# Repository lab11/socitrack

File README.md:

TotTag
======

TotTag is a wearable device that measures **how close people are to one another**, continuously, with
no infrastructure in the room. Each device carries an ultra-wideband (UWB) radio and ranges against
every other device nearby twice a second, recording distances to on-board flash. Nothing is installed
in the environment, nothing is transmitted during a deployment, and no audio or video is captured.

If you are interested in using TotTag in your own research, please fill out this
[Interest Form](https://forms.gle/SqWca9DrKpcx9rBL6).

> **Note: This system is under heavy development and is provided as-is, with no mechanism for external
> support, technical or otherwise. In the future, once the project has reached a steady state and
> staffing has ramped up, we may begin providing limited support. We will post any updates on that
> front here. Thank you for your understanding!**

Documentation
-------------

**All user documentation lives at [lab11.github.io/socitrack](https://lab11.github.io/socitrack/),
built from [`docs/`](docs/).**

Start with [Running a Deployment](docs/running-a-deployment.md) if you want to use TotTag, or
[Getting Started](docs/getting-started.md) if you have devices that have never been set up.

Repository layout
-----------------

| Directory | Contents |
| --- | --- |
| [`docs/`](docs/) | All user and developer documentation; the source of the documentation site |
| [`software/`](software/) | Device firmware and the tools that configure devices and read their data |
| [`hardware/`](hardware/) | Board designs, bills of materials, and enclosure CAD |
| [`media/`](media/) | Photographs and diagrams used by the documentation |

TotTag saw a major platform refresh in 2023, moving to a new hardware and software design built
around the Ambiq Apollo4. Documentation describing the earlier generation is kept under
[`docs/archive/`](docs/archive/).

History, Related Projects, & Relevant Publications
==================================================

This current effort builds on a long line of work exploring the capabilities of
ultra wideband under resource-constrained settings. This repository is an
evolution of projects exploring COTS-based solutions; some others linked below
explore more custom ultra wideband as well.

SociTrack and TotTag Gen 1
--------------------------

- Salo, V. C., Pannuto, P., Hedgecock, W., Biri, A., Russo, D. A., Piersiak, H. A., & Humphreys, K. L. (2022). Measuring naturalistic proximity as a window into caregiver-child interaction patterns. Behavior research methods, 54(4), 1580–1594. https://doi.org/10.3758/s13428-021-01681-8

- Andreas Biri, Neal Jackson, Lothar Thiele, Pat Pannuto, and Prabal Dutta. 2020.
*SociTrack: Infrastructure-Free Interaction Tracking through Mobile Sensor Networks.*
In The 26th Annual International Conference on Mobile Computing and Networking
(MobiCom ’20), September 21–25, 2020, London, United Kingdom. ACM, New York, NY,
USA, 14 pages. https://doi.org/10.1145/3372224.3419190

<!--
- Andreas Biri, Pat Pannuto, and Prabal Dutta. 2019.
*Demo Abstract: Tot-Ternary - A Wearable Platform for Social Interaction Tracking.*
In The 18th International Conference on Information Processing in Sensor Networks
(co-located with CPS-IoT Week 2019) (IPSN ’19), April 16-18, 2019, Montreal, QC,
Canada. ACM, New York, NY, USA, 2 pages. https://doi.org/10.1145/3302506.3312486
-->

<details>
<summary>Legacy documentation from SociTrack / TotTag Gen 1
</summary>

SociTrack
=========

*SociTrack* is a system for using ultra-wideband RF time-of-flight processing to
perform indoor ranging and localization. It incorporates the *SquarePoint*
module, containing a DecaWave DW1000 radio for UWB packet transmission and
timestamping. This module provides node-to-node ranges over an I<sup>2</sup>C
interface which can then be stored locally or transmitted externally.

Hardware
--------

The **SociTrack** system is composed of several hardware pieces. At its core is
the *SquarePoint* module, a 30mm x 15mm PCB that encompasses all of the
core ranging hardware and firmware. *SquarePoint* is provided as an EAGLE board
that allows for direct integration as a design block as part of the
[Lab11 EAGLE library](https://github.com/lab11/eagle). One example of a project
that uses the *SquarePoint* module is the *TotTag*, which comprises an
all-in-one tracking and localization system for mobile nodes. The *TotTag*
hardware includes three UWB antennas and a Bluetooth Low Energy (BLE) radio,
plus a battery charging circuit, SD card for data logging, accelerometer, USB
connectivity, and integrated sensor fusion. TotTag is able to provide ranges and
position estimates directly to a mobile phone application in real-time and can
be configured on-the-fly using a simple user interface over
[Summon](https://github.com/lab11/summon).

### SquarePoint

SquarePoint, an EAGLE design block for UWB ranging, includes the following
components:

- DecaWave DW1000 UWB radio
- STMicroelectronics STM32F091CCU6 MCU
- RF switch

The MCU contains all of the necessary code to control the DW1000 and run the
ranging protocol. This module provides a simple abstraction layer for quick
integration with a carrier board over an I<sup>2</sup>C interface without having
to worry about any underlying implementation details.

### TotTag

The TotTag is a self-contained PCB which utilizes SquarePoint to provide ranging
data for human interaction tracking. It includes:

- The SquarePoint module - 3 UWB antennas
- Nordic Semiconductors nRF52840 BLE radio
- 3.3V LDO designed to be used with 4.2V LiPo batteries
- Battery charge management controller
- SD card holder
- microUSB connector including FTDI FT232R for debugging
- 3-axis accelerometer

The TotTag is designed to be a device that can be used as a ranging anchor, a
mobile tag, or a hybrid combination of both. It offers both infrastructure-free
and infrastructure-based network processing and allows for centimeter-accurate,
multi-day deployments. Both the schematic and board design are open-source and
can be found in the [`hardware/tottag`](hardware/tottag) folder; a suitable 3D
printable case is also provided in
[`hardware/cad/tottag-case`](hardware/cad/tottag-case/).

Software
--------

The SociTrack software is freely available as an open-source Git repository.
When cloning this repository, be sure to do

    git clone --recursive https://github.com/lab11/socitrack.git

or to later run

    git submodule init && git submodule sync

so that all submodules are cloned as well. All of the supporting libraries and
build tools are in submodules for the various hardware platforms used in this
project.

#### SquarePoint

Found in `software/squarepoint` (removed), the core firmware that
enables the SquarePoint module to work includes all of the logic implementing
our custom ranging protocol on top of the DecaWave DW1000 UWB radio. It makes
use of frequency and antenna diversity and leverages both one-way and two-way
ToF ranging to achieve efficient and reliable ranging in various environments.
The firmware architecture supports multiple runtime modalities that can
be selected on-the-fly; currently, we officially support:

- *Standard*: the full ranging protocol, using maximal diversity to achieve
              highly-reliable ranging measurements over 30 different channels.
- *Calibration*: automatically triggered by our calibration scripts, allowing
                 for automated board-specific calibration functions which are
                 then applied to future ranging measurements.

#### TotTag

The TotTag code, located in `software/tottag` (removed),
implements a BLE application that uses the SquarePoint module as an
I<sup>2</sup>C slave and provides for external BLE connectivity. It exposes BLE
services to configure and enable the device, to set the current time to enable
accurate timestamping of ranging data, as well as to access ranging data in
real-time.

#### Mobile App and BLE

The tools in the `software/tottag/mobile_app` (removed)
directory interact with TotTag and read data across the BLE interface. They uses
the Summon app ([Google Play](https://play.google.com/store/apps/details?id=edu.umich.eecs.lab11.summon),
[App Store](https://itunes.apple.com/us/app/summon-lab11/id1051205682)) to
easily access and interact with the TotTag devices. The target website must be
configured in the TotTag code and can be hosted on a personal domain; we
recommend the use of a link shortener to reduce the BLE advertisement length.

### Linux Development

This project requires the [GNU ARM Embedded Toolchain](https://developer.arm.com/open-source/gnu-toolchain/gnu-rm).
Please be aware that the some Linux distros provide out-of-date versions of this
tool; as such, we strongly recommend that you install the newest version
directly from ARM.

</details>

SurePoint
---------

The original projects exploring COTS UWB technology.

PolyPoint introduced the concept of antenna diversity, and demonstrated its
efficacy by finishing as the best-performing UWB-based system at the 2015
Microsoft Indoor Localization competition.

SurePoint expanded on the PolyPoint concepts and built a complete system around
efficient channel diversity, and showed how to scale up robust ranging with
COTS UWB.

- Benjamin Kempke, Pat Pannuto, Bradford Campbell, and Prabal Dutta. 2016.
*SurePoint: Exploiting ultra wideband flooding and diversity to provide robust, scalable, high-fidelity indoor localization.*
In Proceedings of the 14th ACM Conference on Embedded Network Sensor Systems
(SenSys ’16), November 14-16, 2016, Stanford, CA, USA.  ACM, New York, NY,
USA, 13 pages. https://doi.org/10.1145/2994551.2994570

- Benjamin Kempke, Pat Pannuto, and Prabal Dutta. 2015.
*PolyPoint: Guiding indoor quadrotors with ultra-wideband localization.*
In Proceedings of the 2nd International Workshop on Hot Topics in Wireless
(HotWireless ’15), September 11, 2015, Paris, France. ACM, New York, NY,
USA, 5 pages. https://doi.org/10.1145/2799650.2799651

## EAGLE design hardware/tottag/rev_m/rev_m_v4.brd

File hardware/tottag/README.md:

TotTag Revision History
=======================

The original localization platform was developed by the Lab11 research group,
primarily by @bpkempke, @bradjc, and @ppannuto.

The original TotTag hardware (rev_c, rev_d) was developed @abiri during his
Master's Thesis work when he was a visiting scholar with the Lab11 research
group.

Current TotTag hardware is maintained by @ppannuto and @corruptbear.

## "Gen 2" TotTags

Revision I is a fairly complete hardware refresh and board redesign. Initially
necessitated by the COVID-era chip shortage, it became an opportunity to take
advantage of the next generation of low-power MCUs and radio hardware.
Revisions K, L, and M split the board into two physical modules to isolate
design challenges with some of the new chips; revision N re-integrates the
design back to a single module. Revisions O and P center on smaller fixes for
DFM and scale.

### Rev O
Highlights:
 - Connect USB data lines to enable wired offload
 - Remove long-unused hedges and debug (solder jumpers, zero-Ω, and DNP parts; SWTRACE)
 - UWB: Integrate LNA on common signal path for all antennas

[Complete list of Rev O updates](https://github.com/lab11/socitrack/issues/59)

### Rev N
[Rev N updates](https://github.com/lab11/socitrack/issues/58)
__Note: The main board is derived from Rev K, and integrates AP4BP Rev-B back on-board.__
 - Re-integrate AP4BP
    - Remove duplicate concepts (LEDs, TagConnect headers, etc)
    - Match stackup (choose module's 0.6mm for microvias; update 50Ω for all RF)
 - Update IMU to BNO086
 - Update UWB components
    - Generally update design to match new Qorvo app note APH301, bigger things...
       - Revise layout of power rails
       - Update via fencing spacing to lambda/20
       - Remove soldermask from transmission lines
    - Switch from DW3210 (QFN) to DW3110 (WLCSP aka BGA)
       - WCSNG group reports BGA more reliable part
       - Next-gen part QM33110W [released; no stock; pin compatible; update when able] is BGA only
    - Revert from TCXO to XTAL (new rec'd components available)
    - Update key passives to 0603 C0G Low-ESL variants
    - Add Qorvo LNA
       - This rev hedges and only adds to RF1 trace; later rev will move to RFC if fruitful
       - This rev does not add optional band-pass filter
       - Also adds VR3, another copy of the low-noise LDO
  - DFM work
    - Shrink top-metal traces on AP4 BGA perimeter to 5 mil to better match trace 75% of ball pad diameter guidance
    - Add dedicated clean areas for mouse bite tabs
    - Update some passives to Worthington's "ideal" smd component footprint
    - Swap IOM's for DW and 9DOF to ease routing
    - Remove most microvias not on BGA pads

### Rev M + AP4BP Rev-B
[Rev L Issues / Rev M updates](https://github.com/lab11/socitrack/issues/49)
 - Fix silkscreen error on switch label

### Rev L + AP4BP Rev-B
[Prior rev's issues / updates](https://github.com/lab11/socitrack/issues/46)
 - Fixes first-rev issues from the AP4BP module.
 - Rips out our UWB in favor of DWM3000 pre-fab modules for Qorvo as a hedge
   to facilitate more certain-to-work UWB in the short term (but sacrificing
   diversity and robustness [and adding cost]).

### Rev K + AP4BP Rev-A
[Rev I Issues / Rev K Updates](https://github.com/lab11/socitrack/issues/44)
 - (n.b., there is no Rev J to avoid I/J confusion)
 - Move to Apollo4 Blue Plus (Blue has too many silicon bugs)
    - Split this to a castellated module for separation of hw design concerns
 - Move to TCXO for DW3000 (bad idea; will be removed next rev)

### Rev I ***(Major Revision)***
 - Refresh part selection to replace 2015 parts with improved modern versions
 - Major change: Apollo4 Blue as sole MCU
 - Major change: DW3000 replaces DW1000 as UWB transceiver
 - Really, most stuff changed except the wireless charging

## "Gen 1" TotTags

Revisions C–H mark the first generation of TotTag hardware, i.e., that designed
primarily as hardare for social interaction tracking. Generation 1 TotTags
carry a lot of design decisions from the original indoor localization system,
and are generally built on "2010-2020" era technologies.

### Rev H
[Rev G Issues / Rev H Updates](https://github.com/lab11/socitrack/issues/9)
 - Isolates high-bandwidth accelerometer to dedicated SPI bus
 - Revises wireless charging design for robustness
 - Resolve RTC design issues
 - DFM cleanups

### Rev G
[Rev F Issues / Rev G Updates](https://github.com/lab11/totternary/issues/7)
 - Add detachable battery connector
 - Add power switch
 - Adapt PCB shape for mass-production case

### Rev F

[Rev E Issues / Rev F Updates.](https://github.com/lab11/totternary/issues/4)
 - Add RTC

### Rev E

[Rev D Issues / Rev E Updates.](https://github.com/lab11/totternary/issues/3)

Rev E updates:
 - Major performance improvements
   - Revise routing, part layout to improve RF performance
   - Capacitor layout around nRF to fix crystal stability issues
 - Add optional switching regulator bypass

### Rev D

[Rev D Issue.](https://github.com/lab11/totternary/issues/2)

Rev D updates:
 - Add low battery indication
 - Testpoints for buses
 - Fix reset signal for nRF52840
 - Several PCB improvements

### Rev C

[Rev C](../tritag/rev_c/)

Revision C was the first of the 'tottag' family of revisions (though not yet
named as such). It converted the previous hardware modularity into Eagle design
blocks, and was the first single-board revision. It added several features
(storage, sensors) that were not part of the tritag design.

Rev C Major Highlights:
  - Modularize (design block) ranging design
  - Update BLE to nRF52840
  - Add SD Card
  - Add Accelerometer
  - Update charging design
  - Integrate FTDI

## Older revisions

Prior iterations of this platform were developed for the "Polypoint" project,
which later became the "Surepoint" project.

The tottag hardware is largely an evolution of the
[tritag](https://github.com/lab11/polypoint/tree/master/pcb/tritag) module
from these projects.

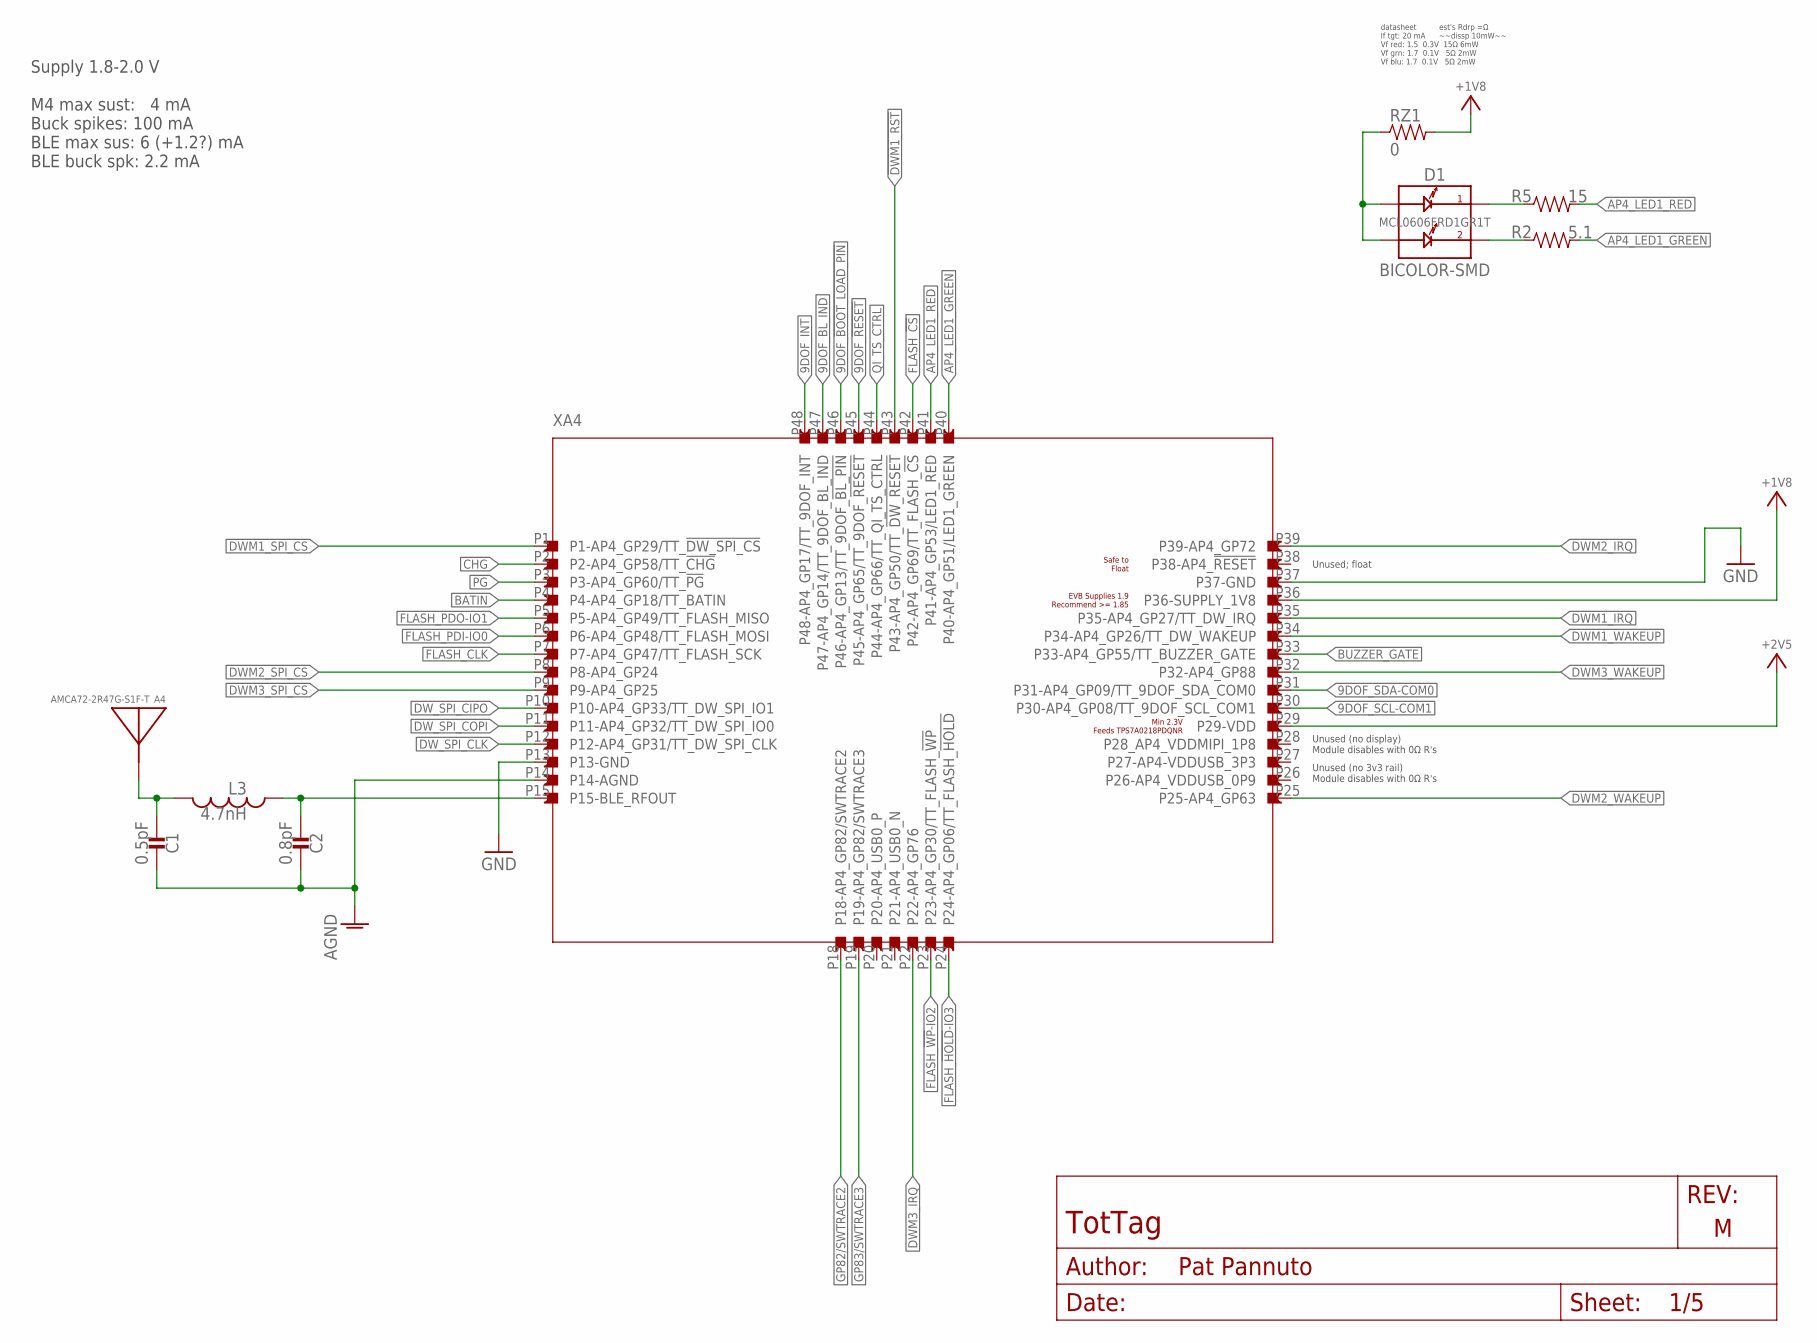
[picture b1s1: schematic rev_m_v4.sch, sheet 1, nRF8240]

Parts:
A4: AMCA72-2R47G-S1F-T; AMCA72-2R470G-S1F-T
C1: 0.5pF; 0402_CAP; MPN GJM1555C1HR50WB01D
C2: 0.8pF; 0402_CAP; MPN GJM1555C1HR80WB01D
D1: BICOLOR-SMD; LED-0606; MPN MCL0606FRD1GR1T
L3: 4.7nH; 0402_CAP; MPN LQW15AN4N7G8ZD
R2: 5.1; 0402_RES; MPN RC0402JR-075R1L
R5: 15; 0402_RES; MPN RC0402JR-0715RL
RZ1: 0; 0603-RES; MPN RMCF0603ZT0R00
XA4: APOLLO4_BLUEPLUS_MODULE

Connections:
9DOF_!BOOT_LOAD_PIN: XA4.P46 (P46-AP4_GP13/TT_9DOF_!BL_PIN); also elsewhere on the board
9DOF_!RESET: XA4.P45 (P45-AP4_GP65/TT_9DOF_!RESET); also elsewhere on the board
9DOF_BL_IND: XA4.P47 (P47-AP4_GP14/TT_9DOF_BL_IND); also elsewhere on the board
9DOF_INT: XA4.P48 (P48-AP4_GP17/TT_9DOF_INT); also elsewhere on the board
9DOF_SCL-COM1: XA4.P30 (P30-AP4_GP08/TT_9DOF_SCL_COM1); also elsewhere on the board
9DOF_SDA-COM0: XA4.P31 (P31-AP4_GP09/TT_9DOF_SDA_COM0); also elsewhere on the board
!CHG: XA4.P2 (P2-AP4_GP58/TT_!CHG); also elsewhere on the board
!DWM1_RST: XA4.P43 (P43-AP4_GP50/TT_!DW_RESET); also elsewhere on the board
!DWM1_SPI_CS: XA4.P1 (P1-AP4_GP29/TT_!DW_SPI_CS); also elsewhere on the board
!DWM2_SPI_CS: XA4.P8 (P8-AP4_GP24); also elsewhere on the board
!DWM3_SPI_CS: XA4.P9 (P9-AP4_GP25); also elsewhere on the board
!PG: XA4.P3 (P3-AP4_GP60/TT_!PG); also elsewhere on the board
+1V8: RZ1.2, XA4.P36 (P36-SUPPLY_1V8); also elsewhere on the board
+2V5: XA4.P29 (P29-VDD); also elsewhere on the board
AGND: C1.2, C2.2, XA4.P14 (P14-AGND)
AP4_LED1_GREEN: R2.2, XA4.P40 (P40-AP4_GP51/LED1_GREEN)
AP4_LED1_RED: R5.2, XA4.P41 (P41-AP4_GP53/LED1_RED)
AP4_LED2_BLUE_COMM: D1.C1, R5.1
AP4_LED_RED_COMM: D1.C2, R2.1
AP4_RFIOP: C2.1, L3.2, XA4.P15 (P15-BLE_RFOUT)
BATIN: XA4.P4 (P4-AP4_GP18/TT_BATIN); also elsewhere on the board
BLE_ANT_FEED: A4.S1, C1.1, L3.1
BUZZER_GATE: XA4.P33 (P33-AP4_GP55/TT_BUZZER_GATE); also elsewhere on the board
DWM1_IRQ: XA4.P35 (P35-AP4_GP27/TT_DW_IRQ); also elsewhere on the board
DWM1_WAKEUP: XA4.P34 (P34-AP4_GP26/TT_DW_WAKEUP); also elsewhere on the board
DWM2_IRQ: XA4.P39 (P39-AP4_GP72); also elsewhere on the board
DWM2_WAKEUP: XA4.P25 (P25-AP4_GP63); also elsewhere on the board
DWM3_IRQ: XA4.P22 (P22-AP4_GP76); also elsewhere on the board
DWM3_WAKEUP: XA4.P32 (P32-AP4_GP88); also elsewhere on the board
DW_SPI_CIPO: XA4.P10 (P10-AP4_GP33/TT_DW_SPI_IO1); also elsewhere on the board
DW_SPI_CLK: XA4.P12 (P12-AP4_GP31/TT_DW_SPI_CLK); also elsewhere on the board
DW_SPI_COPI: XA4.P11 (P11-AP4_GP32/TT_DW_SPI_IO0); also elsewhere on the board
FLASH_!CS: XA4.P42 (P42-AP4_GP69/TT_FLASH_!CS); also elsewhere on the board
FLASH_!HOLD!-IO3: XA4.P24 (P24-AP4_GP06/TT_FLASH_!HOLD); also elsewhere on the board
FLASH_!WP!-IO2: XA4.P23 (P23-AP4_GP30/TT_FLASH_!WP); also elsewhere on the board
FLASH_CLK: XA4.P7 (P7-AP4_GP47/TT_FLASH_SCK); also elsewhere on the board
FLASH_PDI-IO0: XA4.P6 (P6-AP4_GP48/TT_FLASH_MOSI); also elsewhere on the board
FLASH_PDO-IO1: XA4.P5 (P5-AP4_GP49/TT_FLASH_MISO); also elsewhere on the board
GND: XA4.P13 (P13-GND), XA4.P37 (P37-GND); also elsewhere on the board
GP82/SWTRACE2: XA4.P18 (P18-AP4_GP82/SWTRACE2); also elsewhere on the board
GP83/SWTRACE3: XA4.P19 (P19-AP4_GP82/SWTRACE3); also elsewhere on the board
LED_SUP: D1.A1, D1.A2, RZ1.1
QI_TS_CTRL: XA4.P44 (P44-AP4_GP66/TT_QI_TS_CTRL); also elsewhere on the board

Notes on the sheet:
Supply 1.8-2.0 V M4 max sust: 4 mA Buck spikes: 100 mA BLE max sus: 6 (+1.2?) mA BLE buck spk: 2.2 mA
Unused (no 3v3 rail) Module disables with 0Ω R's
Unused (no display) Module disables with 0Ω R's
datasheet est's Rdrp =Ω If tgt: 20 mA ~~dissp 10mW~~ Vf red: 1.5 0.3V 15Ω 6mW Vf grn: 1.7 0.1V 5Ω 2mW Vf blu: 1.7 0.1V 5Ω 2mW
Unused; float

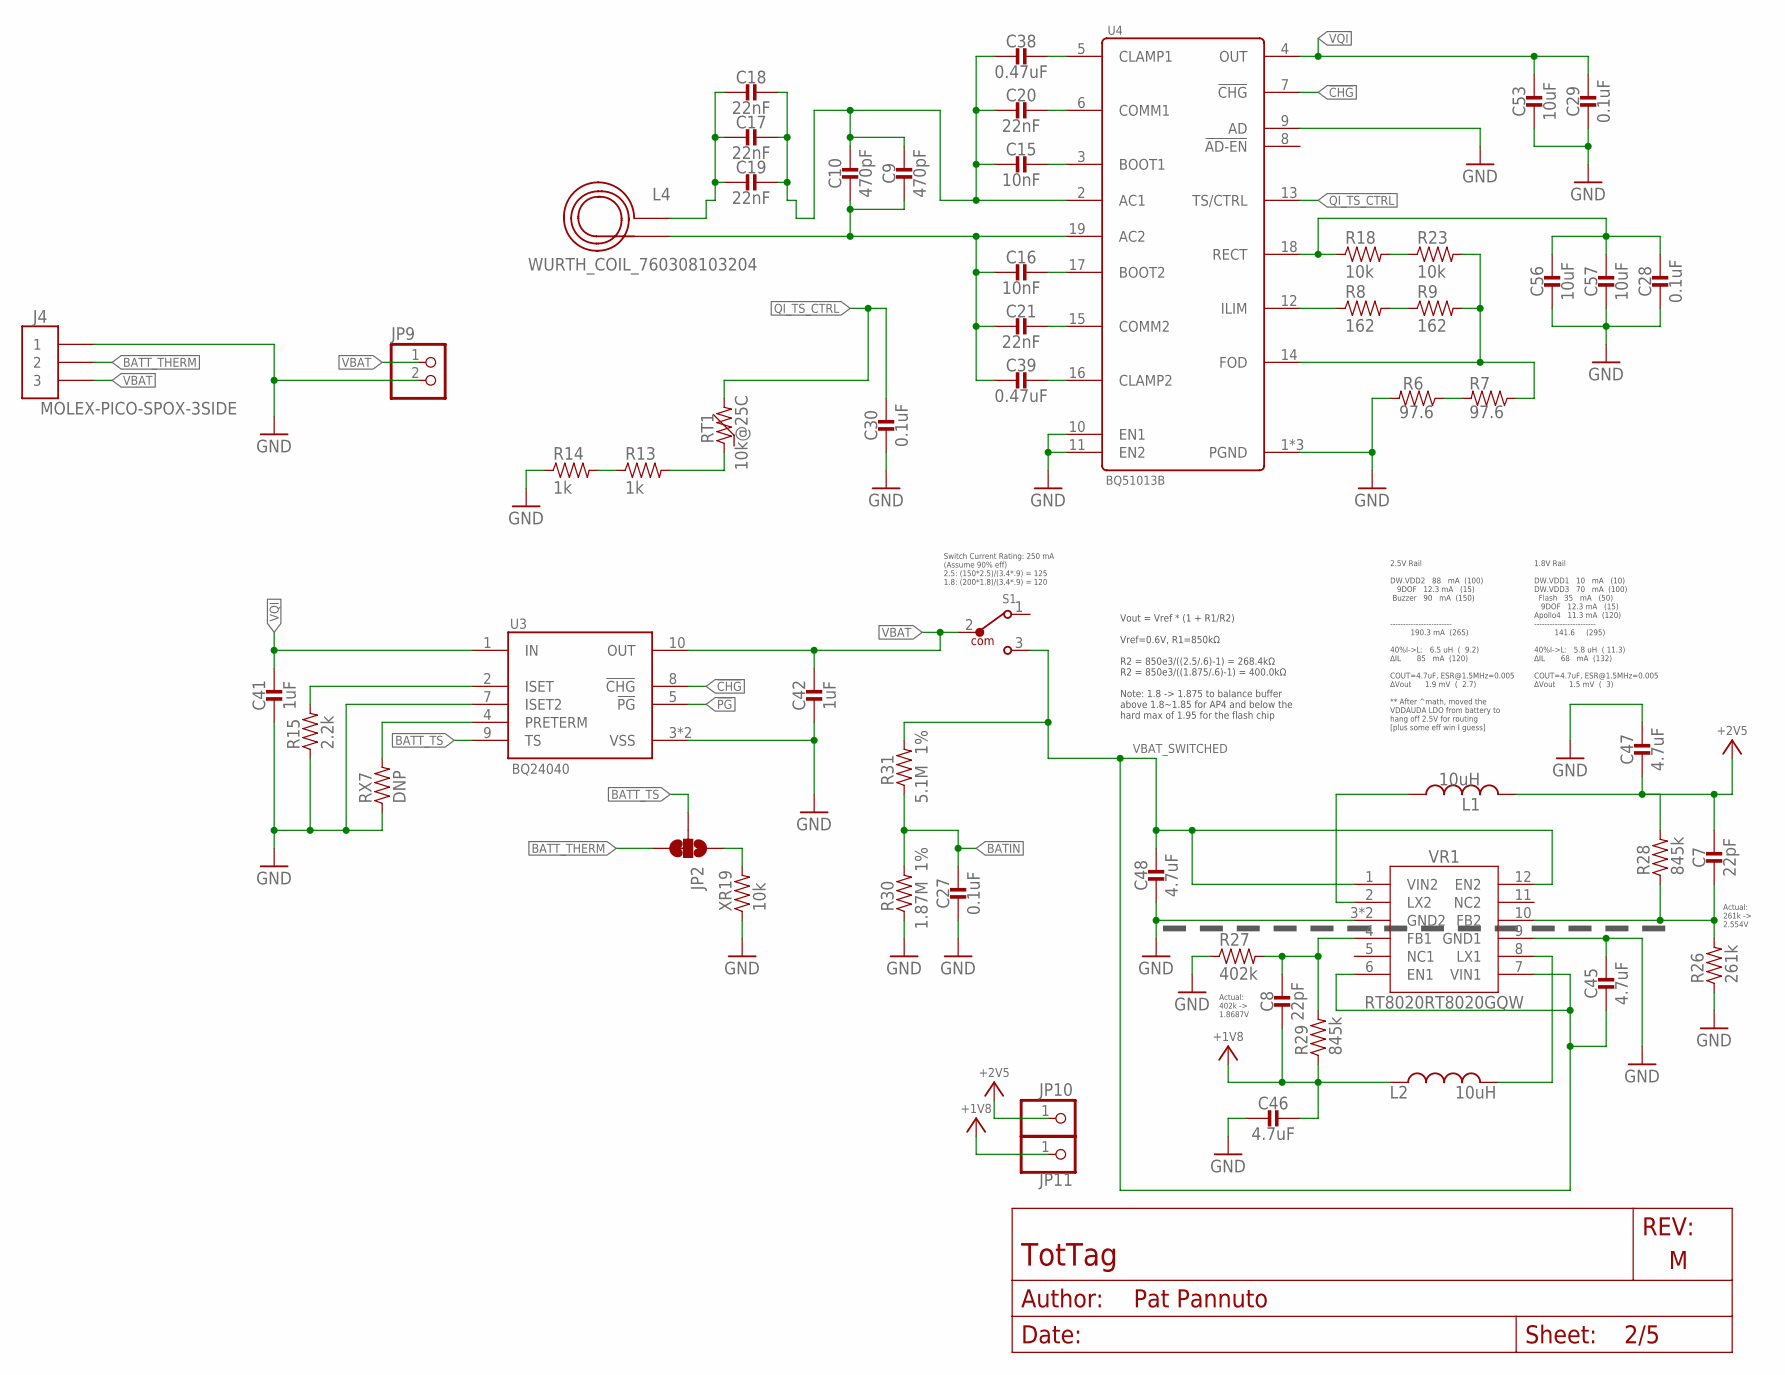
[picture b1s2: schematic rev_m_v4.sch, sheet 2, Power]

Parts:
C7, C8: 22pF; 0201_CAP; MPN GRM0335C1H220FA01D
C9, C10: 470pF; 0402_CAP; MPN GRM1555C1H471JA01J; DIGIKEY 490-6242-1-ND
C15, C16: 10nF; 0402_CAP; MPN GRM155R71H103KA88J; DIGIKEY 490-6351-2-ND
C17, C18, C19: 22nF; 0402_CAP; MPN GRM155R71E223JA61D; DIGIKEY 490-10699-2-ND
C20, C21: 22nF; 0402_CAP; MPN CC0402ZRY5V8BB223; DIGIKEY 311-3823-1-ND
C27, C28, C29, C30: 0.1uF; 0402_CAP; MPN GRM155R71C104KA88J; DIGIKEY 490-6328-1-ND
C38, C39: 0.47uF; 0402_CAP; MPN GRT155R61E474ME01D; DIGIKEY 490-12270-1-ND
C41, C42: 1uF; 0402_CAP; MPN GRM155R70J105KA12J
C45, C46, C47, C48: 4.7uF; 0603_CAP; MPN C1608X7S1A475K080AC
C53, C56, C57: 10uF; 0603_CAP; MPN CM105X5R106M25AT; DIGIKEY 1253-CM105X5R106M25ATCT-ND
J4: MOLEX-PICO-SPOX-3SIDE; MOLEX-PICO-SPOX-3_SIDE
JP2: JUMPER-SMT_3_1-NC_TRACE_SILK; SMT-JUMPER_3_1-NC_TRACE_SILK
JP9: PINHD-1X2; 1X02
JP10, JP11: PINHD-1X1; 1X01
L1, L2: 10uH; NRX3015; MPN NR3015T100M
L4: WURTH_COIL_760308103204
R6, R7: 97.6; 0402_RES; MPN RMCF0402FT97R6; DIGIKEY RMCF0402FT97R6CT-ND
R8, R9: 162; 0402_RES; MPN RMCF0402FT162R; DIGIKEY RMCF0402FT162RCT-ND
R13, R14: 1k; 0402_RES
R15: 2.2k; 0402_RES; MPN RMCF0402JT2K20; DIGIKEY RMCF0402JT2K20CT-ND
R18, R23: 10k; 0402_RES; MPN RC0402JR-0710KL; DIGIKEY 311-10KJRCT-ND
R26: 261k; 0201_RES; MPN ERJ-1GNF2613C
R27: 402k; 0201_RES; MPN ERJ-1GNF4023C
R28, R29: 845k; 0201_RES; MPN ERJ-1GNF8453C
R30: 1.87M; 0402_RES; TOLERANCE 1%; MPN RMCF0402FT1M87
R31: 5.1M; 0402_RES; TOLERANCE 1%; MPN RMCF0402FT5M10; DIGIKEY RMCF0402FT5M10CT-ND
RT1: 10k@25C; 0402_RES; MPN NCU15XH103F60RC; DIGIKEY 490-18149-1-ND
RX7: DNP; 0402_RES
S1: 450404015514; DIGIKEY 732-13665-1-ND
U3: BQ24040; DSQ0010A
U4: BQ51013B; RHL0020A
VR1: RT8020RT8020GQW; SON45P300X300X80-13T160X250N
XR19: 10k; 0402_RES; MPN RC0402JR-0710KL; DIGIKEY 311-10KJRCT-ND

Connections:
!CHG: U3.8 (!CHG), U4.7 (!CHG); also elsewhere on the board
!PG: U3.5 (!PG); also elsewhere on the board
+1V8: C8.P$2 (2), C46.1, JP11.1, L2.P$1 (1), R29.1; also elsewhere on the board
+2V5: C7.P$1 (1), C47.2, JP10.1, L1.P$2 (2), R28.2; also elsewhere on the board
BATIN: C27.1, R30.2, R31.1; also elsewhere on the board
BATT_THERM: J4.2, J4.2SUPP (2), JP2.3
BATT_TS: JP2.2, U3.9 (TS)
BQ_AC1: C9.1, C10.1, C15.2, C17.1, C18.1, C19.1, C20.2, C38.2, U4.2 (AC1)
BQ_AC2: C9.2, C10.2, C16.2, C21.2, C39.2, L4.P$2 (2), U4.19 (AC2)
BQ_BOOT1: C15.1, U4.3 (BOOT1)
BQ_BOOT2: C16.1, U4.17 (BOOT2)
BQ_CLAMP1: C38.1, U4.5 (CLAMP1)
BQ_CLAMP2: C39.1, U4.16 (CLAMP2)
BQ_COMM1: C20.1, U4.6 (COMM1)
BQ_COMM2: C21.1, U4.15 (COMM2)
BQ_FOD: R7.1, R9.2, R23.2, U4.14 (FOD)
BQ_ILM: R8.1, U4.12 (ILIM)
BQ_ISET: R15.2, U3.2 (ISET)
BQ_RECT: C28.1, C56.1, C57.1, R18.1, U4.18 (RECT)
COIL_AC1: C17.2, C18.2, C19.2, L4.P$1 (1)
GND: C27.2, C28.2, C29.2, C30.2, C41.2, C42.2, C45.1, C46.2, C47.1, C48.2, C53.2, C56.2, C57.2, J4.1, J4.1SUPP (1), JP9.2, R6.2, R14.1, R15.1, R26.1, R27.1, R30.1, RX7.1, U3.3 (VSS), U3.7 (ISET2), U3.PAD (VSS), U4.1 (PGND), U4.9 (AD), U4.10 (EN1), U4.11 (EN2), U4.20 (PGND), U4.PAD (PGND), VR1.3 (GND2), VR1.9 (GND1), VR1.13 (GND2), XR19.1; also elsewhere on the board
unnamed: R6.1, R7.2
unnamed: JP2.1, XR19.2
unnamed: RX7.2, U3.4 (PRETERM)
unnamed: R18.2, R23.1
unnamed: R8.2, R9.1
unnamed: R13.2, RT1.1
unnamed: R13.1, R14.2
QI_TS_CTRL: C30.1, RT1.2, U4.13 (TS/CTRL); also elsewhere on the board
VBAT: C42.1, J4.3, J4.3SUPP (3), JP9.1, S1.2, U3.10 (OUT)
VBAT_SWITCHED: C45.2, C48.1, R31.2, S1.3, VR1.1 (VIN2), VR1.6 (EN1), VR1.7 (VIN1), VR1.12 (EN2); also elsewhere on the board
VQI: C29.1, C41.1, C53.1, U3.1 (IN), U4.4 (OUT)
VR1_FB1: C8.P$1 (1), R27.2, R29.2, VR1.4 (FB1)
VR1_FB2: C7.P$2 (2), R26.2, R28.1, VR1.10 (FB2)
VR1_LX1: L2.P$2 (2), VR1.8 (LX1)
VR1_LX2: L1.P$1 (1), VR1.2 (LX2)

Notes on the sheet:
2.5V Rail DW.VDD2 88 mA (100) 9DOF 12.3 mA (15) Buzzer 90 mA (150) ------------------------ 190.3 mA (265) 40%I->L: 6.5 uH ( 9.2) ∆IL 85 mA (120) COUT=4.7uF, ESR@1.5MHz=0.005 ∆Vout 1.9 mV ( 2.7) ** After ^math, moved the VDDAUDA LDO from battery to hang off 2.5V for routing [plus some eff win I gue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
1.8V Rail DW.VDD1 10 mA (10) DW.VDD3 70 mA (100) Flash 35 mA (50) 9DOF 12.3 mA (15) Apollo4 11.3 mA (120) ------------------------ 141.6 (295) 40%I->L: 5.8 uH ( 11.3) ∆IL 68 mA (132) COUT=4.7uF, ESR@1.5MHz=0.005 ∆Vout 1.5 mV ( 3)
Vout = Vref * (1 + R1/R2) Vref=0.6V, R1=850kΩ R2 = 850e3/((2.5/.6)-1) = 268.4kΩ R2 = 850e3/((1.875/.6)-1) = 400.0kΩ Note: 1.8 -> 1.875 to balance buffer above 1.8~1.85 for AP4 and below the hard max of 1.95 for the flash chip
Switch Current Rating: 250 mA (Assume 90% eff) 2.5: (150*2.5)/(3.4*.9) = 125 1.8: (200*1.8)/(3.4*.9) = 120
Actual: 402k -> 1.8687V
Actual: 261k -> 2.554V

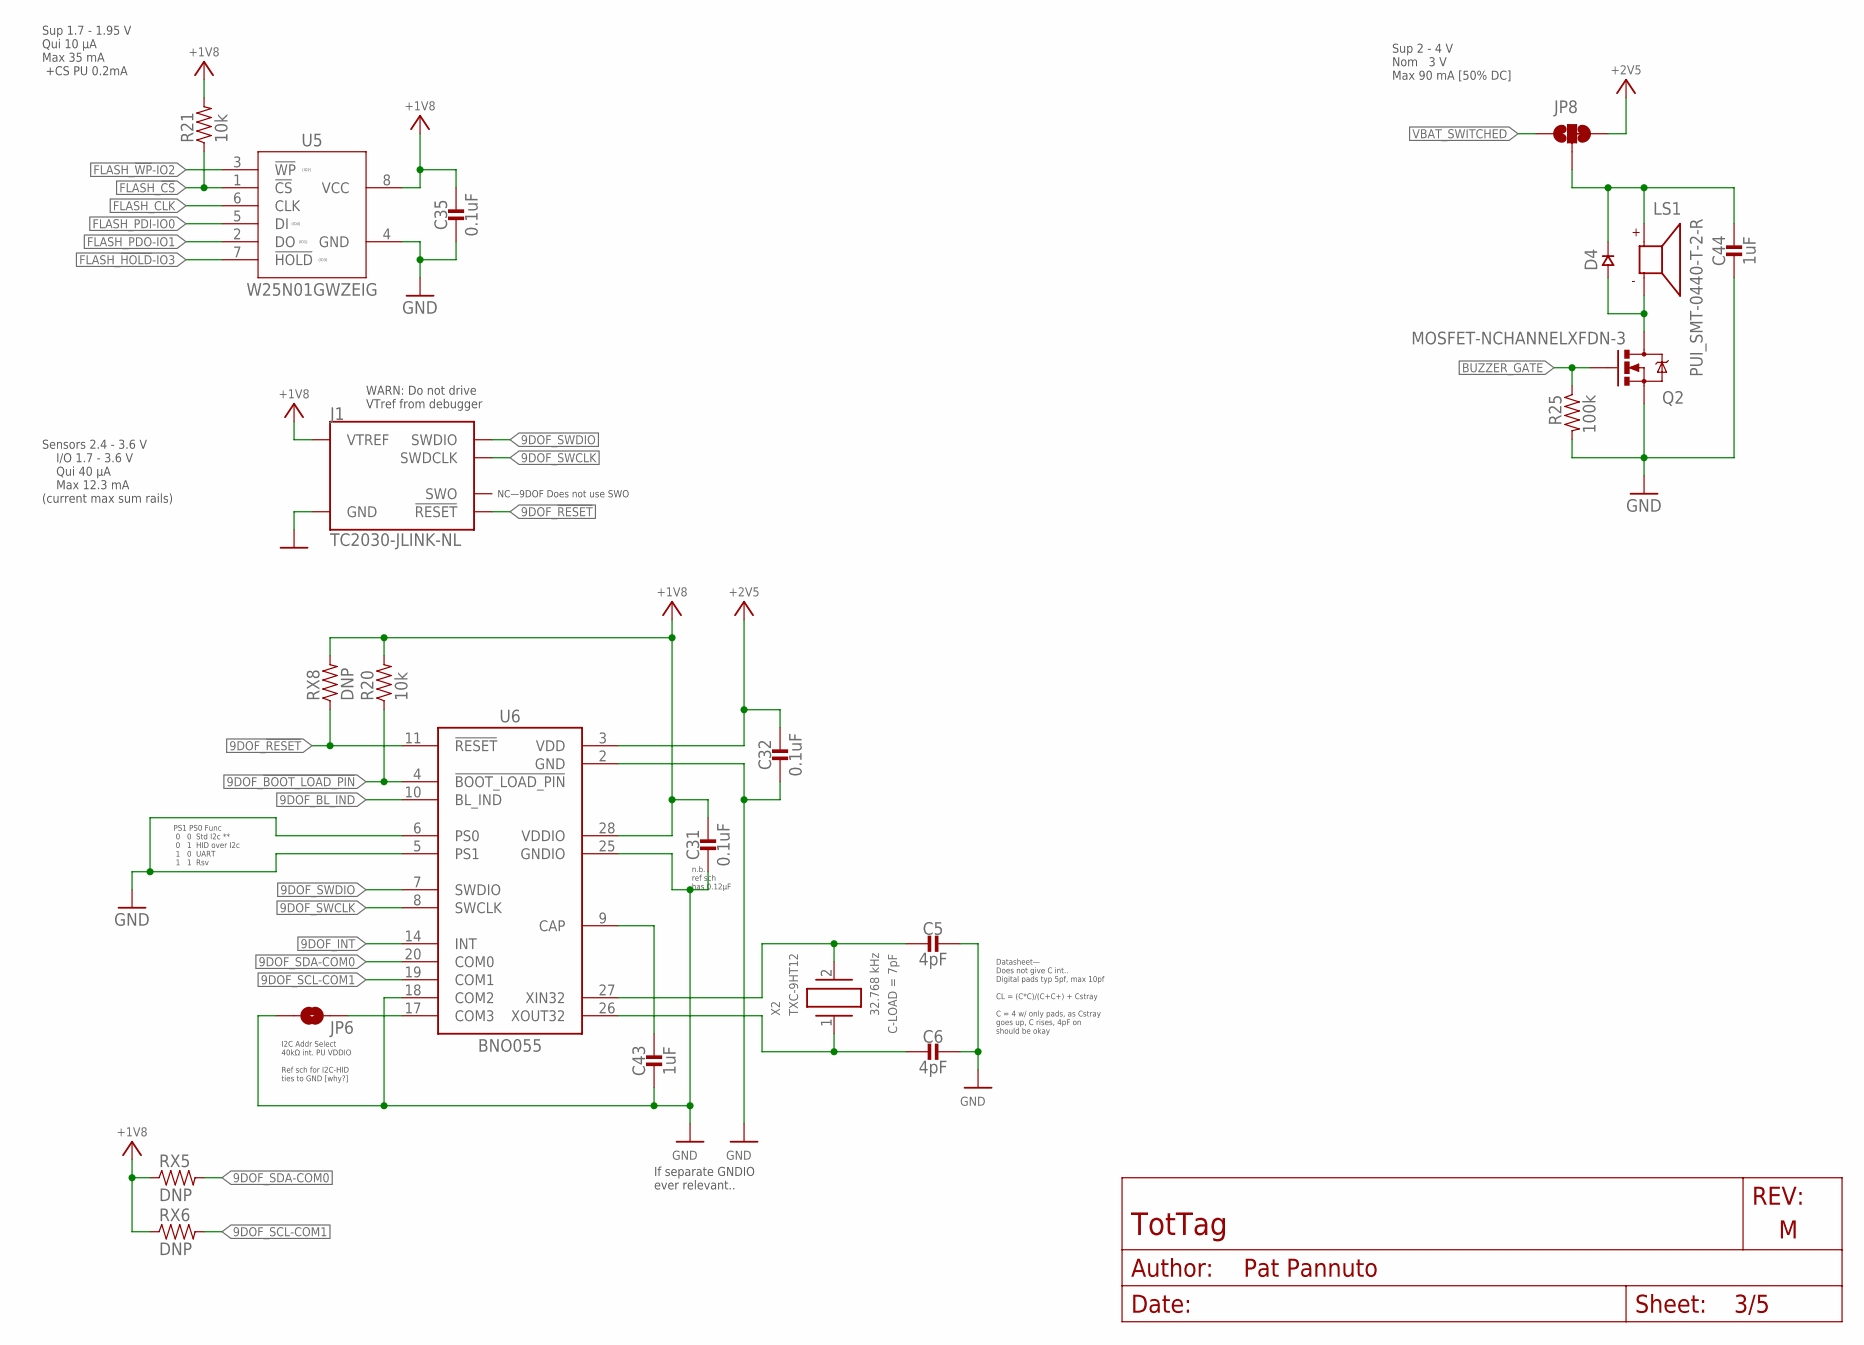
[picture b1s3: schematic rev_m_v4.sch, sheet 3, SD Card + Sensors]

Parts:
C5, C6: 4pF; 0201_CAP; MPN GRM0335C1H4R0BA01D
C31, C32, C35: 0.1uF; 0402_CAP; MPN CL05A104KP5NNNC
C43, C44: 1uF; 0402_CAP; MPN GRM155R70J105KA12J
D4: DIODE0402; 0402_DIODE; MPN CDSQR400B-HF; DIGIKEY 641-2087-1-ND
J1: TC2030-JLINK-NL; TC2030-IDC-NL
JP6: JUMPER-SMT_2_NO_SILK; SMT-JUMPER_2_NO_SILK
JP8: JUMPER-SMT_3_1-NC_TRACE_SILK; SMT-JUMPER_3_1-NC_TRACE_SILK
LS1: PUI_SMT-0440-T-2-R; SMT-0440-T-2-R
Q2: MOSFET-NCHANNELXFDN-3; XFDFN-3
R20, R21: 10k; 0402_RES; MPN RC0402JR-0710KL; DIGIKEY 311-10KJRCT-ND
R25: 100k; 0402_RES; MPN RT0402BRE07100KL
RX5, RX6, RX8: DNP; 0603-RES
U5: W25N01GWZEIG; WSON127P800X600X80-9T430X340N
U6: BNO055; LGA28R0P510X4_5P2X3P8X1
X2: TXC-9HT12; MPN 9HT12-32.768KDZY-T

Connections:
9DOF_!BOOT_LOAD_PIN: R20.1, U6.4 (!BOOT_LOAD_PIN); also elsewhere on the board
9DOF_!RESET: J1.3 (!RESET), RX8.1, U6.11 (!RESET); also elsewhere on the board
9DOF_BL_IND: U6.10 (BL_IND); also elsewhere on the board
9DOF_CAP: C43.1, U6.9 (CAP)
9DOF_INT: U6.14 (INT); also elsewhere on the board
9DOF_SCL-COM1: RX6.2, U6.19 (COM1); also elsewhere on the board
9DOF_SDA-COM0: RX5.2, U6.20 (COM0); also elsewhere on the board
9DOF_SWCLK: J1.4 (SWDCLK), U6.8 (SWCLK)
9DOF_SWDIO: J1.2 (SWDIO), U6.7 (SWDIO)
9DOF_XI: C5.P$2 (2), U6.27 (XIN32), X2.2
9DOF_XO: C6.P$2 (2), U6.26 (XOUT32), X2.1
+1V8: C31.1, C35.1, J1.1 (VTREF), R20.2, R21.2, RX5.1, RX6.1, RX8.2, U5.8 (VCC), U6.28 (VDDIO); also elsewhere on the board
+2V5: C32.1, JP8.3, U6.3 (VDD); also elsewhere on the board
BUZZER_GATE: Q2.G, R25.1; also elsewhere on the board
BUZZER_SUPPLY: C44.1, D4.CATHODE, JP8.2, LS1.+
FLASH_!CS: R21.1, U5.1 (!CS); also elsewhere on the board
FLASH_!HOLD!-IO3: U5.7 (!HOLD); also elsewhere on the board
FLASH_!WP!-IO2: U5.3 (!WP); also elsewhere on the board
FLASH_CLK: U5.6 (CLK); also elsewhere on the board
FLASH_PDI-IO0: U5.5 (DI); also elsewhere on the board
FLASH_PDO-IO1: U5.2 (DO); also elsewhere on the board
GND: C5.P$1 (1), C6.P$1 (1), C31.2, C32.2, C35.2, C43.2, C44.2, J1.5 (GND), JP6.1, Q2.S, R25.2, U5.4 (GND), U6.2 (GND), U6.5 (PS1), U6.6 (PS0), U6.18 (COM2), U6.25 (GNDIO); also elsewhere on the board
unnamed: D4.ANODE, LS1.- (N), Q2.D
unnamed: JP6.2, U6.17 (COM3)
VBAT_SWITCHED: JP8.1; also elsewhere on the board

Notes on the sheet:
Sup 1.7 - 1.95 V Qui 10 µA Max 35 mA +CS PU 0.2mA
Sensors 2.4 - 3.6 V I/O 1.7 - 3.6 V Qui 40 µA Max 12.3 mA (current max sum rails)
Sup 2 - 4 V Nom 3 V Max 90 mA [50% DC]
PS1 PS0 Func 0 0 Std I2c ** 0 1 HID over I2c 1 0 UART 1 1 Rsv
If separate GNDIO ever relevant..
I2C Addr Select 40kΩ int. PU VDDIO Ref sch for I2C-HID ties to GND [why?]
n.b. ref sch has 0.12µF
WARN: Do not drive VTref from debugger
Datasheet— Does not give C int.. Digital pads typ 5pf, max 10pf CL = (C*C)/(C+C+) + Cstray C = 4 w/ only pads, as Cstray goes up, C rises, 4pF on should be okay
NC—9DOF Does not use SWO

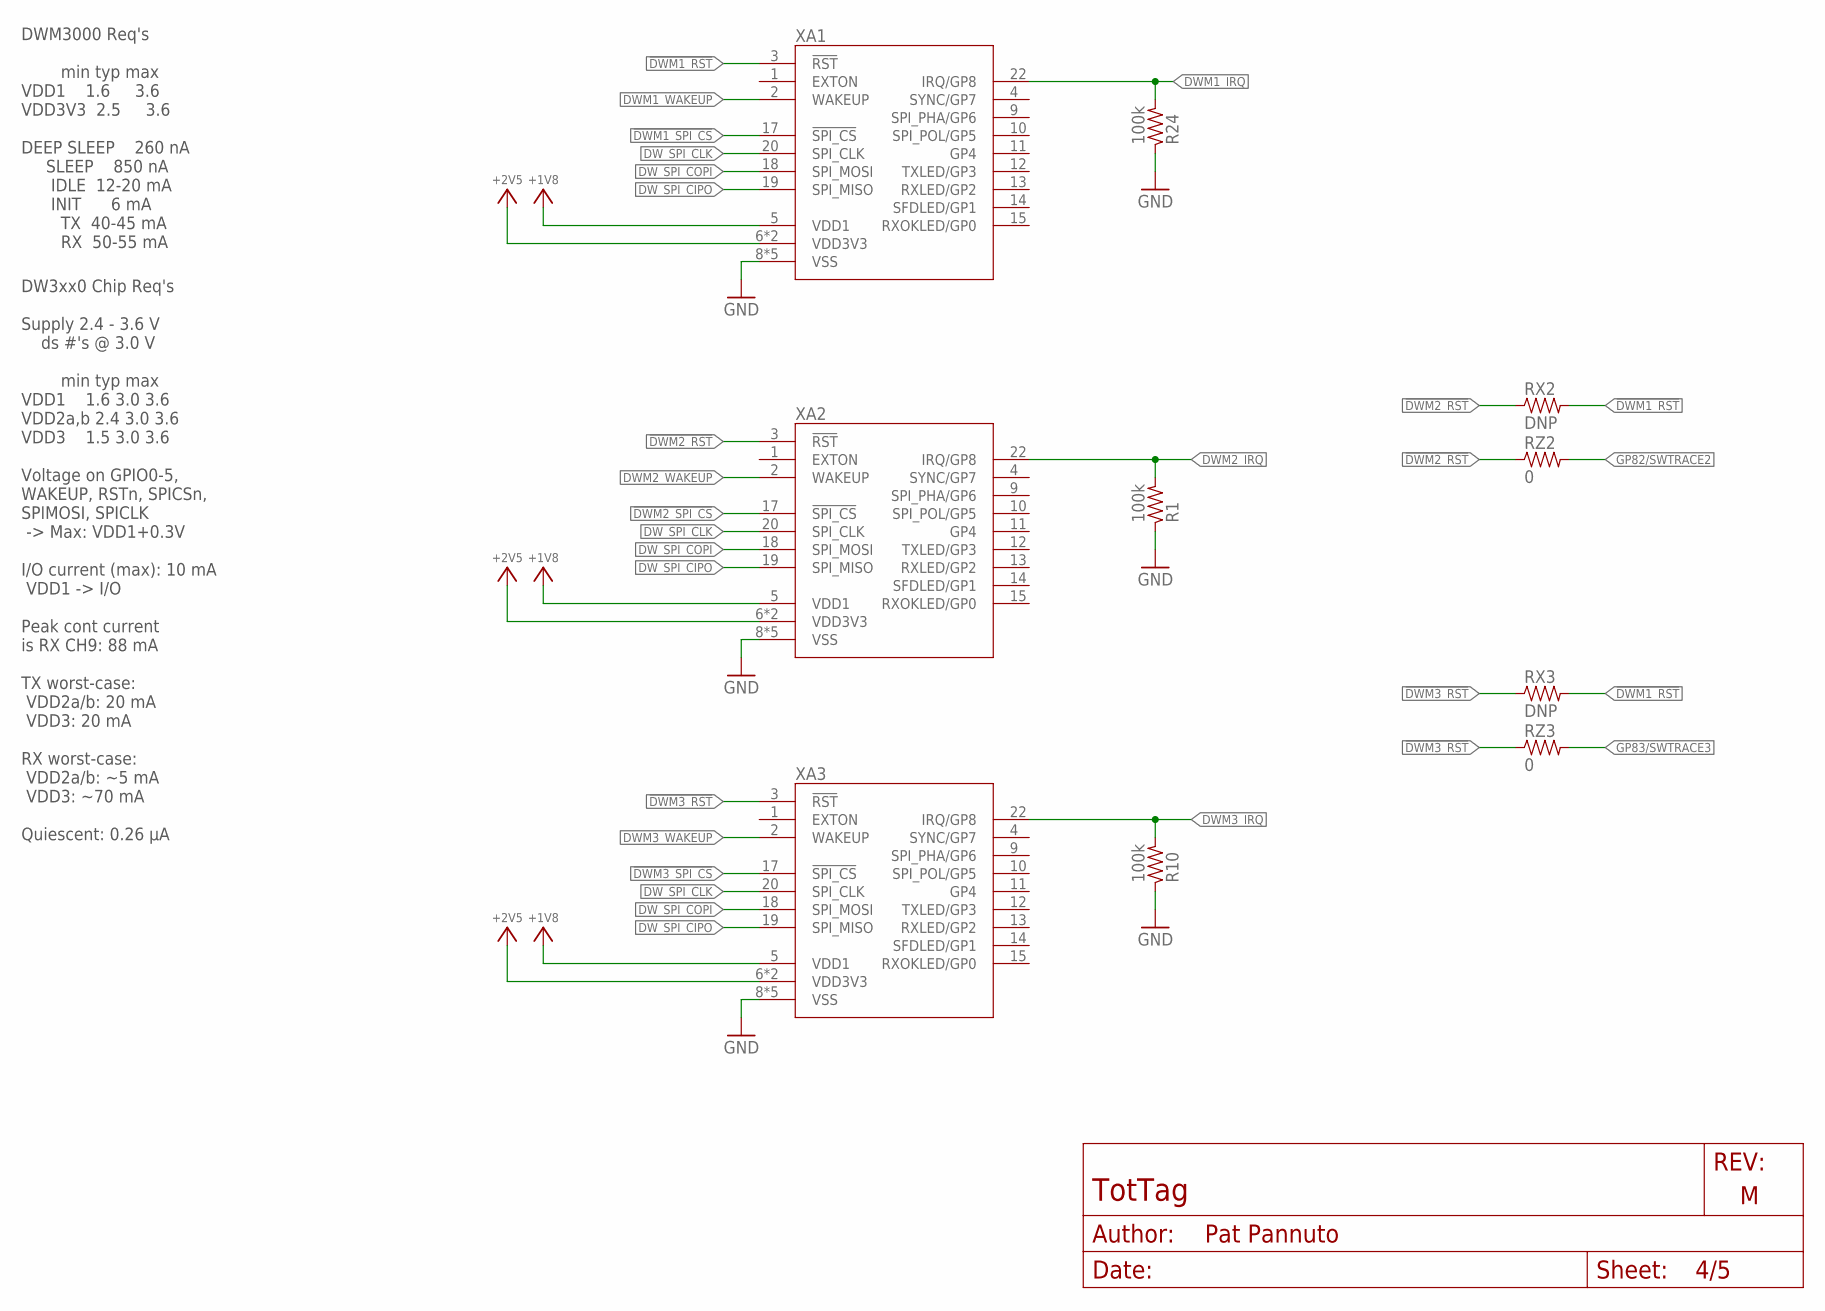
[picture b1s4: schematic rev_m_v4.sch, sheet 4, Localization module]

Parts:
R1, R10, R24: 100k; 0402_RES; MPN RT0402BRE07100KL
RX2, RX3: DNP; 0603-RES
RZ2, RZ3: 0; 0603-RES; MPN RMCF0603ZT0R00
XA1, XA2, XA3: DWM3000

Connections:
!DWM1_RST: RX2.2, RX3.2, XA1.3 (!RST); also elsewhere on the board
!DWM1_SPI_CS: XA1.17 (!SPI_CS); also elsewhere on the board
!DWM2_RST: RX2.1, RZ2.1, XA2.3 (!RST)
!DWM2_SPI_CS: XA2.17 (!SPI_CS); also elsewhere on the board
!DWM3_RST: RX3.1, RZ3.1, XA3.3 (!RST)
!DWM3_SPI_CS: XA3.17 (!SPI_CS); also elsewhere on the board
+1V8: XA1.5 (VDD1), XA2.5 (VDD1), XA3.5 (VDD1); also elsewhere on the board
+2V5: XA1.6 (VDD3V3), XA1.7 (VDD3V3), XA2.6 (VDD3V3), XA2.7 (VDD3V3), XA3.6 (VDD3V3), XA3.7 (VDD3V3); also elsewhere on the board
DWM1_IRQ: R24.2, XA1.22 (IRQ/GP8); also elsewhere on the board
DWM1_WAKEUP: XA1.2 (WAKEUP); also elsewhere on the board
DWM2_IRQ: R1.2, XA2.22 (IRQ/GP8); also elsewhere on the board
DWM2_WAKEUP: XA2.2 (WAKEUP); also elsewhere on the board
DWM3_IRQ: R10.2, XA3.22 (IRQ/GP8); also elsewhere on the board
DWM3_WAKEUP: XA3.2 (WAKEUP); also elsewhere on the board
DW_SPI_CIPO: XA1.19 (SPI_MISO), XA2.19 (SPI_MISO), XA3.19 (SPI_MISO); also elsewhere on the board
DW_SPI_CLK: XA1.20 (SPI_CLK), XA2.20 (SPI_CLK), XA3.20 (SPI_CLK); also elsewhere on the board
DW_SPI_COPI: XA1.18 (SPI_MOSI), XA2.18 (SPI_MOSI), XA3.18 (SPI_MOSI); also elsewhere on the board
GND: R1.1, R10.1, R24.1, XA1.8 (VSS), XA1.16 (VSS), XA1.21 (VSS), XA1.23 (VSS), XA1.24 (VSS), XA2.8 (VSS), XA2.16 (VSS), XA2.21 (VSS), XA2.23 (VSS), XA2.24 (VSS), XA3.8 (VSS), XA3.16 (VSS), XA3.21 (VSS), XA3.23 (VSS), XA3.24 (VSS); also elsewhere on the board
GP82/SWTRACE2: RZ2.2; also elsewhere on the board
GP83/SWTRACE3: RZ3.2; also elsewhere on the board

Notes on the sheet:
DW3xx0 Chip Req's Supply 2.4 - 3.6 V ds #'s @ 3.0 V min typ max VDD1 1.6 3.0 3.6 VDD2a,b 2.4 3.0 3.6 VDD3 1.5 3.0 3.6 Voltage on GPIO0-5, WAKEUP, RSTn, SPICSn, SPIMOSI, SPICLK -> Max: VDD1+0.3V I/O current (max): 10 mA VDD1 -> I/O Peak cont current is RX CH9: 88 mA TX worst-case: VDD2a/b: 20 mA VDD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
DWM3000 Req's min typ max VDD1 1.6 3.6 VDD3V3 2.5 3.6 DEEP SLEEP 260 nA SLEEP 850 nA IDLE 12-20 mA INIT 6 mA TX 40-45 mA RX 50-55 mA

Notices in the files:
parts and their libraries:
SparkFun-Aesthetics: Licensing: Creative Commons ShareAlike 4.0 International - https://creativecommons.org/licenses/by-sa/4.0
SparkFun-LED: Licensing: CC v3.0 Share-Alike You are welcome to use this library for commercial purposes.
Wurth_Switch_WS-SLSU: Copyright: Würth Elektronik
